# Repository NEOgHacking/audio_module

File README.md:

# audio_module

This is a simple audio module to use headphones on the hackxpansion console, this is a simple module with a 3.5mm audio jack.

## Design
For this design i wanted to be able to connect my headphones to thee console for audio output to add an extra dimension to the games.
For this i used a PCM5102A audio chip from Texas Instruments to drive the audio output on the 3.5mm headphone jack. I tried to isolate the digital power and analog power as good as possible with a ferrite bead to prevent unwanted output from interference from the digital side.

## Schematic
This design was made in KiCad 10 and uses the standard parts. I needed to make a custom part for the audio port the PJ-342, i could use the symbol from KiCad but had to make my own footprint.

This is a pretty basic schematic but it should work.

## Layout

The layout was based on the hackxpansion console to fit in 1 module bay. It uses a simple 2 layer PCB with a gnd fill on top and bottom layer to make an as good as possible gnd plane for the audio chip.

## Case
The case was made in onshape using the free licence, its pretty simple and was based on an import of the PCB so referencing was easy. The PCB screws in from the bottom with 2 screws to attach it to the case.

Here is the [onshape link](https://cad.onshape.com/documents/23acd3255b900cc5b85fa1fc/w/7ef244823df79fb773706f50/e/46ef782e0da3cdec777ec4b8?renderMode=0&uiState=6a7f842a860458379a62dd10)

## Software
WIP
The software was made as described in the first driver tutorial. It was heavily edited to create I2S compatibility for the audio chip, this however is still not in a working state, i am working hard to get it working but it is not that easy to get working for me because i am shit in rust.

# BOM

|Vendor|Price in $|Tax in $   |
|------|----------|-----------|
|LCSC  |10.42     |10.47      |
|JLCPCB|4.00      |6.80       |

# Credits
Huge thanks to @Koeg for the YSWS and all the help with the firmware!!

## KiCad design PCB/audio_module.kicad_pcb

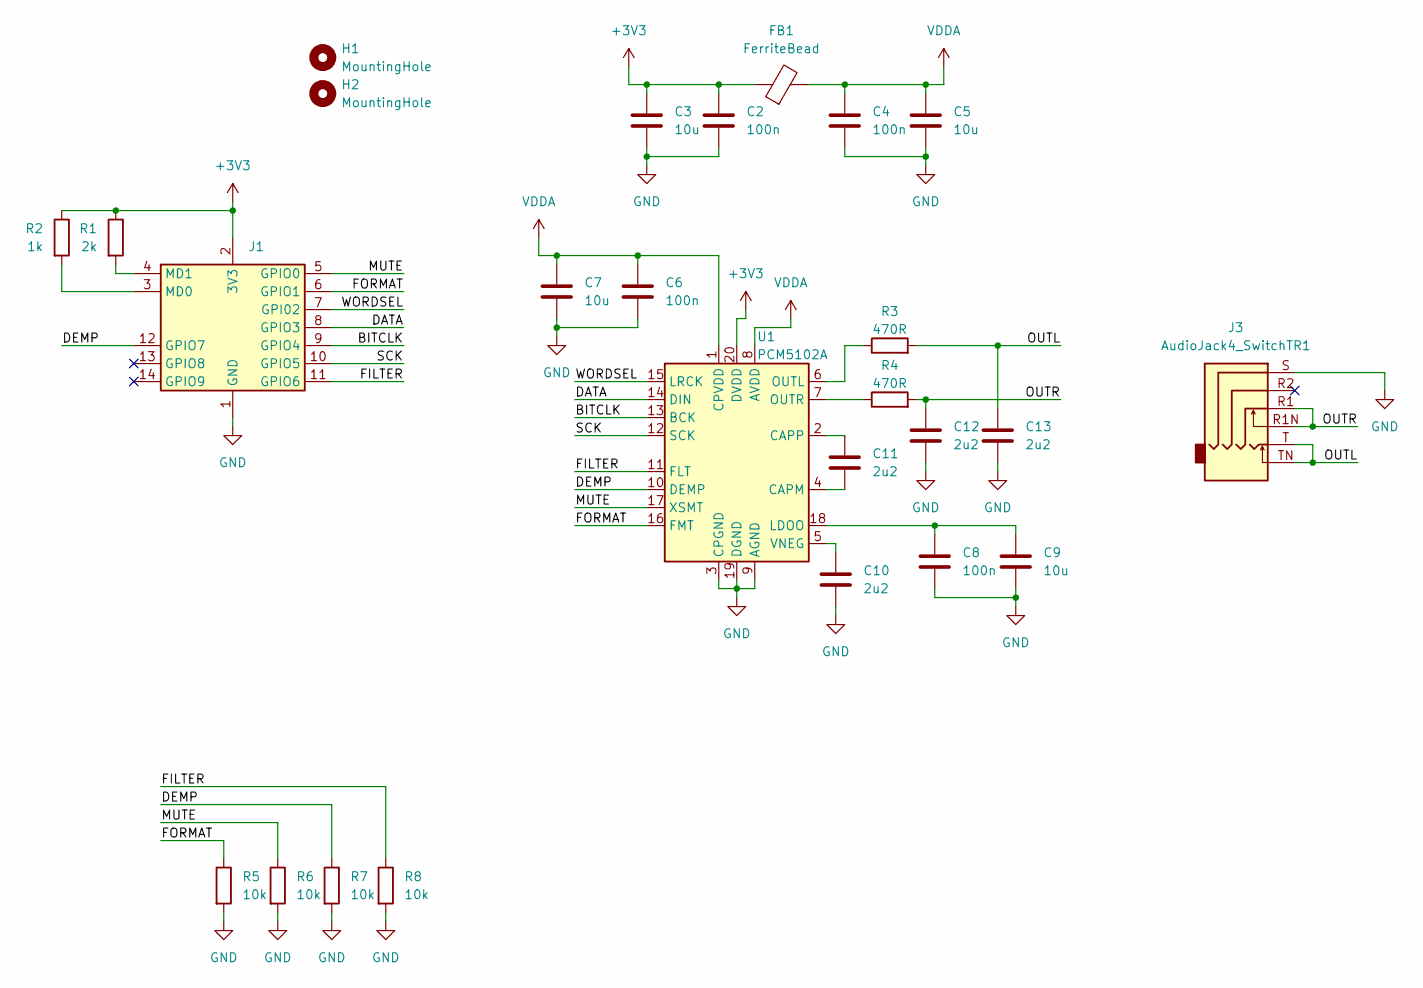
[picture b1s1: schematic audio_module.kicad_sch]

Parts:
C2, C4, C6, C8: 100n; C_0603_1608Metric
C3, C5, C7, C9: 10u; C_0603_1608Metric
C10, C11, C12, C13: 2u2; C_0603_1608Metric
FB1: FerriteBead; L_0603_1608Metric; LCSC C14709
H1, H2: MountingHole; MountingHole_2.2mm_M2
J1: Male_Module
J3: AudioJack4_SwitchTR1; PJ-342; LCSC C668606
R1: 2k; R_0805_2012Metric_Pad1.20x1.40mm_HandSolder
R2: 1k; R_0805_2012Metric_Pad1.20x1.40mm_HandSolder
R3, R4: 470R; R_0603_1608Metric
R5, R6, R7, R8: 10k; R_0603_1608Metric
U1: PCM5102A; TSSOP-20_4.4x6.5mm_P0.65mm; LCSC C107671

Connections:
+3V3: C2.1, C3.1, FB1.1, J1.2 (3V3), R1.1, R2.1, U1.20 (DVDD)
/BITCLK: J1.9 (GPIO4), U1.13 (BCK)
/DATA: J1.8 (GPIO3), U1.14 (DIN)
/DEMP: J1.12 (GPIO7), R7.1, U1.10 (DEMP)
/FILTER: J1.11 (GPIO6), R8.1, U1.11 (FLT)
/FORMAT: J1.6 (GPIO1), R5.1, U1.16 (FMT)
/MUTE: J1.5 (GPIO0), R6.1, U1.17 (XSMT)
/OUTL: C13.1, J3.T, J3.TN, R3.2
/OUTR: C12.1, J3.R1, J3.R1N, R4.2
/SCK: J1.10 (GPIO5), U1.12 (SCK)
/WORDSEL: J1.7 (GPI02), U1.15 (LRCK)
GND: C2.2, C3.2, C4.2, C5.2, C6.2, C7.2, C8.2, C9.2, C10.2, C12.2, C13.2, J1.1 (GND), J3.S, R5.2, R6.2, R7.2, R8.2, U1.3 (CPGND), U1.9 (AGND), U1.19 (DGND)
unnamed: J1.3 (MD0), R2.2
unnamed: J1.4 (MD1), R1.2
unnamed: C11.2, U1.4 (CAPM)
unnamed: C11.1, U1.2 (CAPP)
unnamed: C8.1, C9.1, U1.18 (LDOO)
unnamed: R3.1, U1.6 (OUTL)
unnamed: R4.1, U1.7 (OUTR)
unnamed: C10.1, U1.5 (VNEG)
VDDA: C4.1, C5.1, C6.1, C7.1, FB1.2, U1.1 (CPVDD), U1.8 (AVDD)

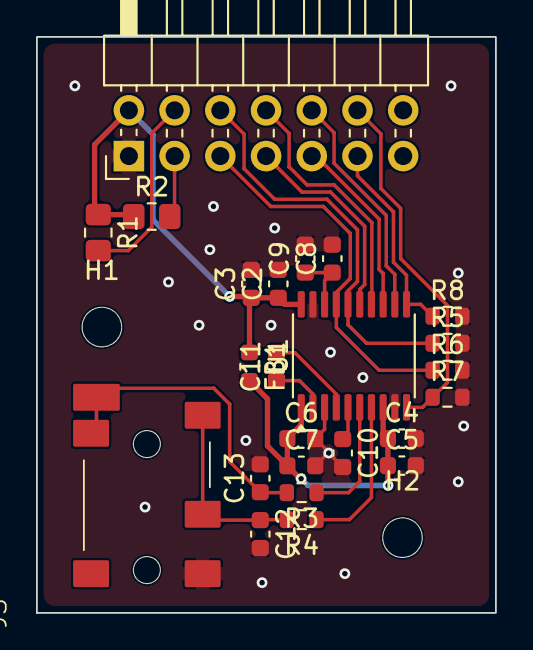
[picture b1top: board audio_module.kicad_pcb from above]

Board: 2 copper layers, 25.5 x 32.0 mm, 26 parts (0 on the bottom side), 21 nets.
